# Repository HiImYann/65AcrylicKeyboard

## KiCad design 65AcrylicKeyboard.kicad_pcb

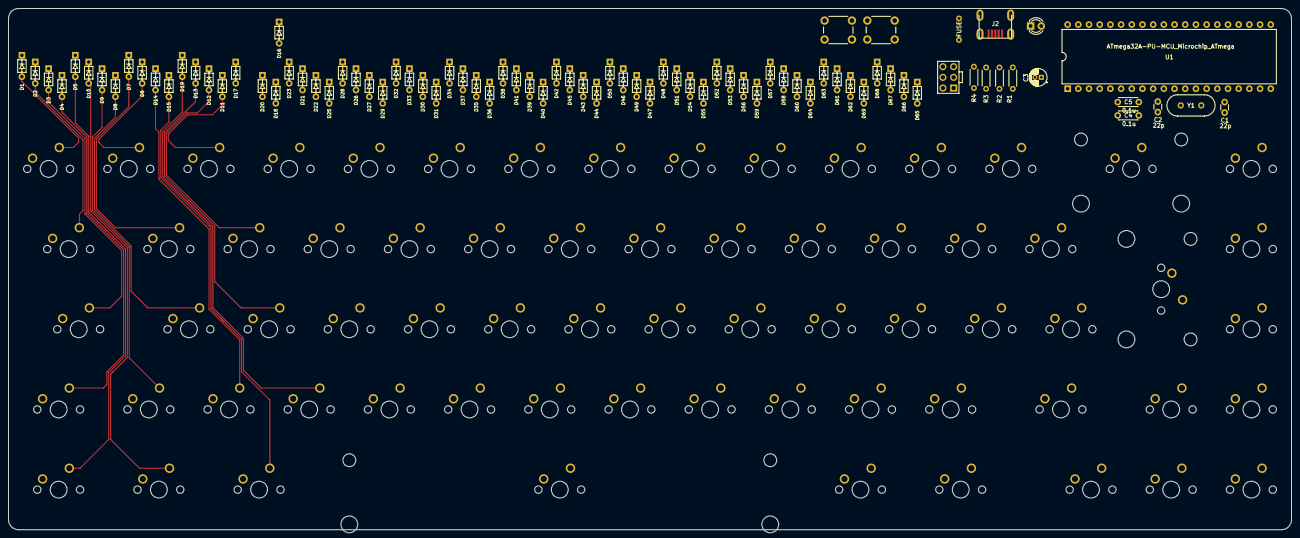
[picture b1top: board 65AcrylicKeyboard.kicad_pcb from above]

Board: 2 copper layers, 304.8 x 123.8 mm, 153 parts (0 on the bottom side), 97 nets.

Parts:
C1, C2: 22p; C_Disc_D3.0mm_W1.6mm_P2.50mm
C3: 4.7u; CP_Radial_D4.0mm_P1.50mm
C4, C5: 0.1u; C_Disc_D4.3mm_W1.9mm_P5.00mm
D1, D2, D3, D4, D5, D6, D7, D8, D9, D10, D11, D12, D13, D14, D15, D16, D17, D18, D19, D20, D21, D22, D23, D25, D26, D27, D28, D29, D30, D31, D32, D33, D34, D35, D36, D37, D38, D39, D40, D41, D42, D43, D44, D45, D46, D47, D48, D49, D50, D51, D52, D53, D54, D55, D56, D57, D58, D59, D60, D61, D62, D63, D64, D65, D66, D67, D68, D69: D_Small; D_DO-35_SOD27_P5.08mm_Horizontal
D24: POWER LED; LED_D3.0mm
F1: 500mA; polyfuse_5.1mm
J1: AVR-ISP-6; AVR_ICSP_3x2
J2: USB_B_Micro; Molex-0548190589
K1: KEYSW; MXOnly-1.5U-NoLED
K2, K57: KEYSW; MXOnly-1.75U-NoLED
K3, K4, K9, K14, K48, K53: KEYSW; MXOnly-1.25U-NoLED
K5, K6, K7, K8, K10, K11, K12, K13, K15, K16, K17, K18, K19, K20, K21, K22, K23, K24, K25, K26, K27, K28, K29, K30, K32, K33, K34, K35, K36, K37, K38, K39, K40, K41, K42, K43, K44, K45, K46, K47, K49, K50, K51, K52, K54, K55, K56, K58, K61, K62, K63, K64, K65, K66, K67: KEYSW; MXOnly-1U-NoLED
K31: KEYSW; MXOnly-6.25U-NoLED
K59: KEYSW; MXOnly-2U-NoLED
K60: KEYSW; MXOnly-ISO-ROTATED-ReversedStabilizers-NoLED
K?1: KEYSW; MXOnly-1U-NoLED
R1: 1.5K; R_Axial_DIN0204_L3.6mm_D1.6mm_P5.08mm_Horizontal
R2, R3: 75R; R_Axial_DIN0204_L3.6mm_D1.6mm_P5.08mm_Horizontal
R4: 10k; R_Axial_DIN0204_L3.6mm_D1.6mm_P5.08mm_Horizontal
SW1: RESET; SW_PUSH_6mm
SW2: BOOT; SW_PUSH_6mm
U1: ATmega32A-PU-MCU_Microchip_ATmega; DIP-40_W15.24mm
Y1: Crystal; Crystal_HC49-4H_Vertical

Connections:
+5V: C3.1, C4.1, C5.1, D24.2, F1.1, J1.2, R4.1
COL0: K1.1, K2.1, K3.1, K4.1, K?1.1
COL1: K5.1, K6.1, K7.1, K8.1, K9.1
COL2: K10.1, K11.1, K12.1, K13.1, K14.1
COL3: K15.1, K16.1, K17.1, K18.1
COL4: K19.1, K20.1, K21.1, K22.1
COL5: K23.1, K24.1, K25.1, K26.1
COL6: K27.1, K28.1, K29.1, K30.1, K31.1
COL7: K32.1, K33.1, K34.1, K35.1
COL8: K36.1, K37.1, K38.1, K39.1
COL9: K40.1, K41.1, K42.1, K43.1
COL10: K44.1, K45.1, K46.1, K47.1, K48.1
COL11: K49.1, K50.1, K51.1, K52.1, K53.1
COL12: K54.1, K55.1, K56.1, K57.1, K58.1
COL13: K59.1, K60.1, K61.1, K62.1
COL14: K63.1, K64.1, K65.1, K66.1, K67.1
GND: C1.2, C2.2, C3.2, C4.2, C5.2, J1.6, J2.5, J2.6, R1.2, SW1.1, SW2.1, U1.11, U1.31
unnamed: C1.1, U1.13, Y1.1
unnamed: C2.1, U1.12, Y1.2
unnamed: D1.2, K?1.2
unnamed: D2.2, K1.2
unnamed: D3.2, K2.2
unnamed: D4.2, K3.2
unnamed: D5.2, K4.2
unnamed: D6.2, K5.2
unnamed: D7.2, K6.2
unnamed: D8.2, K7.2
unnamed: D9.2, K8.2
unnamed: D10.2, K9.2
unnamed: D11.2, K10.2
unnamed: D12.2, K11.2
unnamed: D13.2, K12.2
unnamed: D14.2, K13.2
unnamed: D15.2, K14.2
unnamed: D16.2, K15.2
unnamed: D17.2, K16.2
unnamed: D18.2, K17.2
unnamed: D19.2, K18.2
unnamed: D20.2, K19.2
unnamed: D21.2, K20.2
unnamed: D22.2, K21.2
unnamed: D23.2, K22.2
unnamed: D24.1, R1.1
unnamed: D25.2, K23.2
unnamed: D26.2, K24.2
unnamed: D27.2, K25.2
unnamed: D28.2, K26.2
unnamed: D29.2, K27.2
unnamed: D30.2, K28.2
unnamed: D31.2, K29.2
unnamed: D32.2, K30.2
unnamed: D33.2, K31.2
unnamed: D34.2, K32.2
unnamed: D35.2, K33.2
unnamed: D36.2, K34.2
unnamed: D37.2, K35.2
unnamed: D38.2, K36.2
unnamed: D39.2, K37.2
unnamed: D40.2, K38.2
unnamed: D41.2, K39.2
unnamed: D42.2, K40.2
unnamed: D43.2, K41.2
unnamed: D44.2, K42.2
unnamed: D45.2, K43.2
unnamed: D46.2, K44.2
unnamed: D47.2, K45.2
unnamed: D48.2, K46.2
unnamed: D49.2, K47.2
unnamed: D50.2, K48.2
unnamed: D51.2, K49.2
unnamed: D52.2, K50.2
unnamed: D53.2, K51.2
unnamed: D54.2, K52.2
unnamed: D55.2, K53.2
unnamed: D56.2, K54.2
unnamed: D57.2, K55.2
unnamed: D58.2, K56.2
unnamed: D59.2, K57.2
unnamed: D60.2, K58.2
unnamed: D61.2, K59.2
unnamed: D62.2, K60.2
unnamed: D63.2, K61.2
unnamed: D64.2, K62.2
unnamed: D65.2, K63.2
unnamed: D66.2, K64.2
unnamed: D67.2, K65.2
unnamed: D68.2, K66.2
unnamed: D69.2, K67.2
unnamed: J2.2, R3.2
unnamed: J2.3, R2.2
ROW0: D1.1, D6.1, D11.1, D16.1, D20.1, D25.1, D29.1, D34.1, D38.1, D42.1, D46.1, D51.1, D56.1, D61.1, D65.1
ROW1: D2.1, D7.1, D12.1, D17.1, D21.1, D26.1, D30.1, D35.1, D39.1, D43.1, D47.1, D52.1, D57.1, D62.1, D66.1
ROW2: D3.1, D8.1, D13.1, D18.1, D22.1, D27.1, D31.1, D36.1, D40.1, D44.1, D48.1, D53.1, D58.1, D67.1
ROW3: D4.1, D9.1, D14.1, D19.1, D23.1, D28.1, D32.1, D37.1, D41.1, D45.1, D49.1, D54.1, D59.1, D63.1, D68.1
ROW4: D5.1, D10.1, D15.1, D33.1, D50.1, D55.1, D60.1, D64.1, D69.1
VCC: F1.2, J2.1
reset: J1.5, R4.2, SW1.2
